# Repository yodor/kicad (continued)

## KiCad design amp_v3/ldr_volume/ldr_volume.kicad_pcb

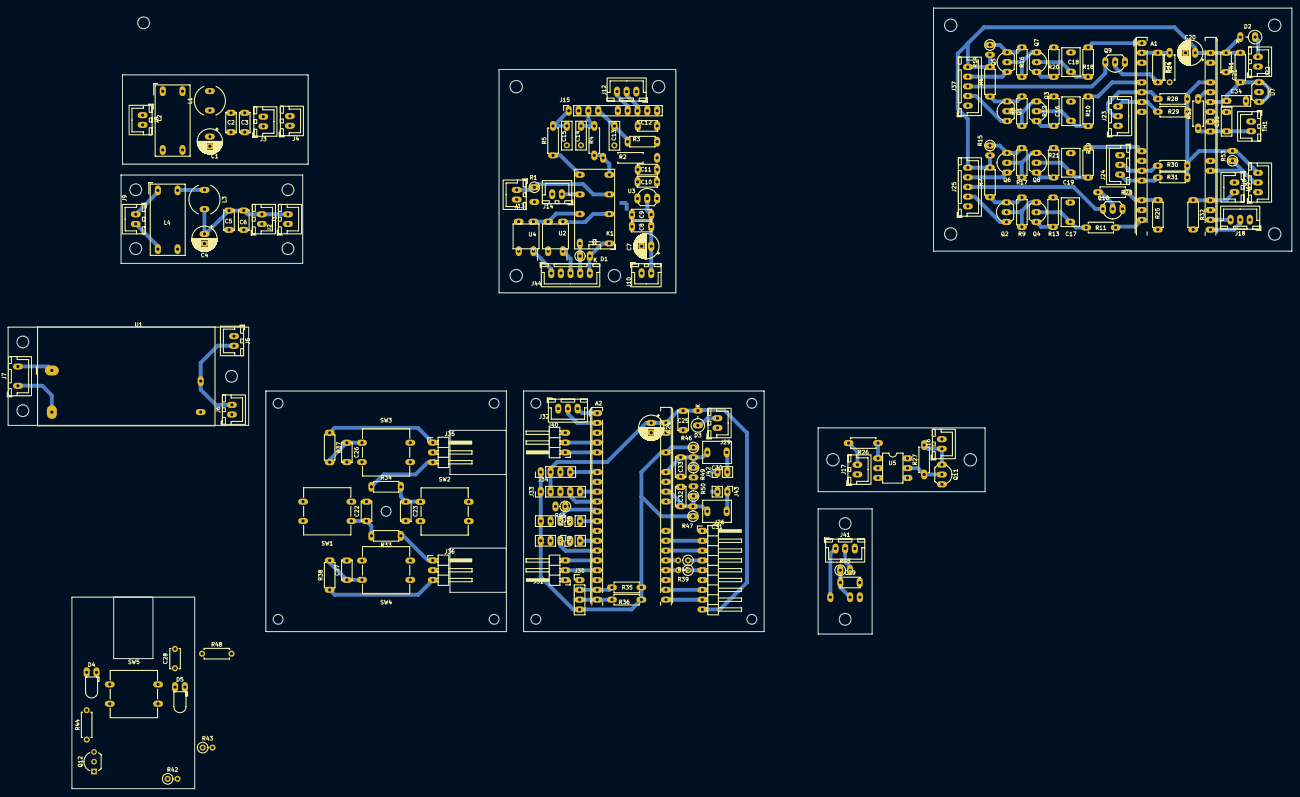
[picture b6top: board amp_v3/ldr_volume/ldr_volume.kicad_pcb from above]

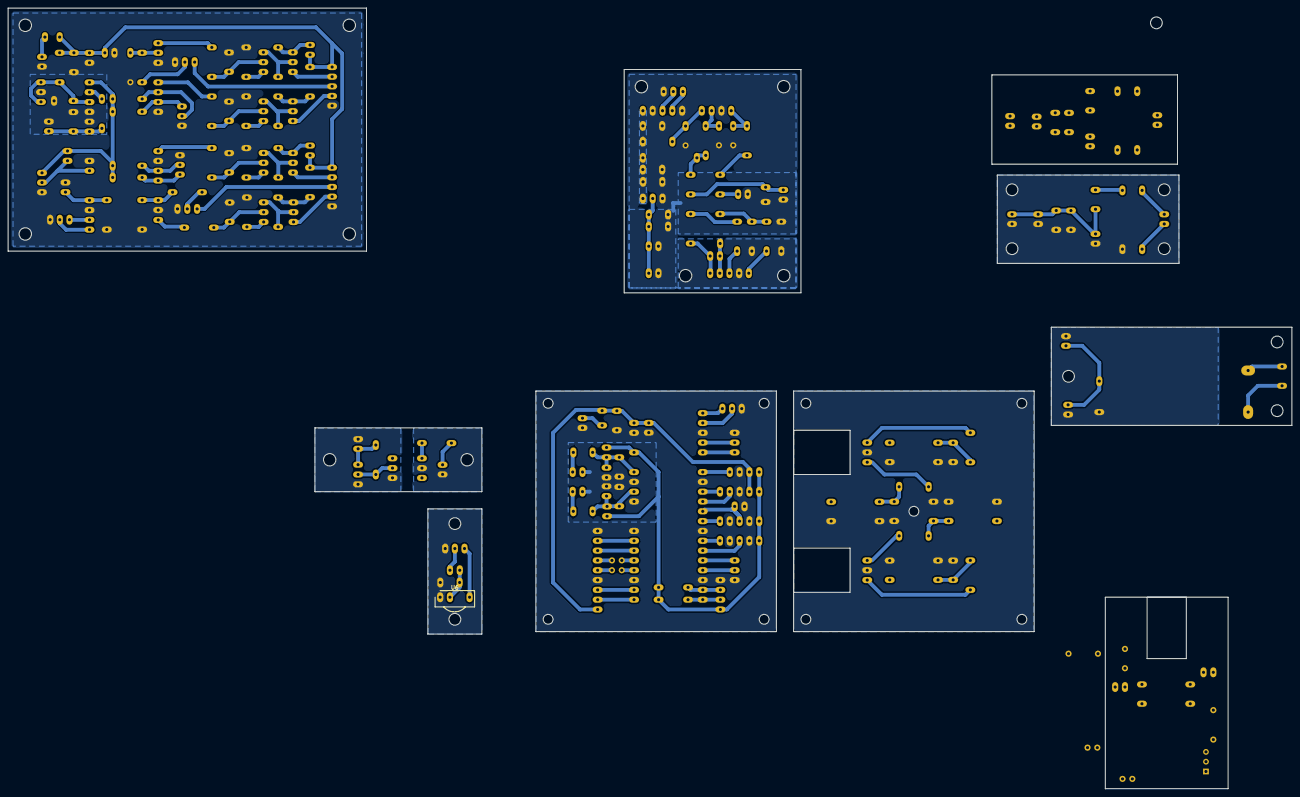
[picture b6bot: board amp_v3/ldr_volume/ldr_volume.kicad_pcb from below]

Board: 2 copper layers, 332.1 x 201.9 mm, 171 parts (5 on the bottom side), 122 nets.

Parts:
A1, A2: RaspberryPi_Pico_W; RaspberryPi_Pico_Common_THT
C1, C4: 100uF (low esr); CP_Radial_D6.3mm_P2.50mm
C2, C5: 10uF; C_Disc_D5.0mm_W2.5mm_P5.00mm
C3, C6: 100nF (X7R); C_Disc_D5.0mm_W2.5mm_P5.00mm
C7: 100uF; CP_Radial_D6.3mm_P2.50mm
C8, C11: 1uF; C_Disc_D5.0mm_W2.5mm_P5.00mm
C9, C10, C12, C21, C22, C23, C25, C26, C27, C28, C29: 100nF; C_Disc_D5.0mm_W2.5mm_P5.00mm
C13, C14, C15, C34, C35: 100nF; C_Rect_L7.2mm_W2.5mm_P5.00mm_FKS2_FKP2_MKS2_MKP2
C16, C17, C18, C19: 1uF; C_Rect_L7.2mm_W4.5mm_P5.00mm_FKS2_FKP2_MKS2_MKP2
C20, C24: 100uF low; CP_Radial_D6.3mm_P2.50mm
C30, C31: 1uF; C_Rect_L7.2mm_W5.5mm_P5.00mm_FKS2_FKP2_MKS2_MKP2
C32, C33: 10nF; C_Disc_D5.0mm_W2.5mm_P5.00mm
D1: 1n4007; D_DO-35_SOD27_P2.54mm_Vertical_CathodeUp
D2, D3: 1n5819; D_DO-41_SOD81_P3.81mm_Vertical_CathodeUp
D4: LED; LED_D3.0mm_Horizontal_O1.27mm_Z2.0mm
D5: WHITE LED; LED_D3.0mm_Horizontal_O1.27mm_Z2.0mm
J1: PWR1; JST_XH_B2B-XH-A_1x02_P2.50mm_Vertical
J2: PWR2; JST_XH_B2B-XH-A_1x02_P2.50mm_Vertical
J3, J5: PWR3; JST_XH_B2B-XH-A_1x02_P2.50mm_Vertical
J4, J6: PWR4; JST_XH_B2B-XH-A_1x02_P2.50mm_Vertical
J7: Conn_01x03_Pin; JST_XH_B3B-XH-A_1x03_P2.50mm_Vertical
J8, J9: 5V_IN; JST_XH_B2B-XH-A_1x02_P2.50mm_Vertical
J10: 5v_in; JST_XH_B2B-XH-A_1x02_P2.50mm_Vertical
J12, J24: I2C_R; JST_XH_B3B-XH-A_1x03_P2.50mm_Vertical
J13: A_IN; JST_XH_B2B-XH-A_1x02_P2.50mm_Vertical
J14: A_OUT; JST_XH_B2B-XH-A_1x02_P2.50mm_Vertical
J15: ADS1115; PinSocket_1x10_P2.54mm_Vertical
J16: MUTE_OUT; JST_XH_B2B-XH-A_1x02_P2.50mm_Vertical
J17, J19: MUTE; JST_XH_B2B-XH-A_1x02_P2.50mm_Vertical
J18, J40: UART; JST_XH_B3B-XH-A_1x03_P2.50mm_Vertical
J22, J29: PWR_IN; JST_XH_B2B-XH-A_1x02_P2.50mm_Vertical
J23: I2C_L; JST_XH_B3B-XH-A_1x03_P2.50mm_Vertical
J25: LDR_R; JST_XH_B5B-XH-A_1x05_P2.50mm_Vertical
J26: TFT; PinHeader_1x09_P2.54mm_Horizontal
J27: PWR_BTN; PinHeader_1x02_P2.54mm_Vertical
J28: PWR_BTN_LED; PinHeader_1x02_P2.54mm_Vertical
J30: I2C; PinHeader_1x04_P2.54mm_Vertical
J31: BTN_VOL; PinHeader_1x03_P2.54mm_Horizontal
J32: BTN_MENU; PinHeader_1x03_P2.54mm_Horizontal
J33: ALPS; PinHeader_1x05_P2.54mm_Vertical
J34: PWR_RLY; PinHeader_1x04_P2.54mm_Vertical
J35: BTN_EXT1; PinHeader_1x03_P2.54mm_Horizontal
J36: BTN_EXT2; PinHeader_1x03_P2.54mm_Horizontal
J37, J44: LDR_L; JST_XH_B5B-XH-A_1x05_P2.50mm_Vertical
J38: IR; PinHeader_1x03_P2.54mm_Vertical
J39: MUTE; PinHeader_1x03_P2.54mm_Vertical
J41: IR_SENSOR; JST_XH_B3B-XH-A_1x03_P2.50mm_Vertical
J42: S_AIN_L; PinHeader_1x02_P2.54mm_Vertical
J43: S_AIN_R; PinHeader_1x02_P2.54mm_Vertical
K1: G5V-2; Relay_DPDT_Omron_G5V-2
L1, L3: 10uH; L_Radial_D7.8mm_P5.00mm_Fastron_07HCP
L2: RN202-0.3-02-12M; Choke_Schaffner_RN202-04-8.8x18.2mm
L4: RN-202-1/02; Choke_Schaffner_RN202-04-8.8x18.2mm
NT1: ATOGNDA; NetTie-2_SMD_Pad1.0o
NT2: AUDIOGND_TO_GNDA; NetTie-2_SMD_Pad1.0o
NT3, NT4: NetTie_2; NetTie-2_SMD_Pad1.0o
Q1, Q2, Q5, Q6: BC557; TO-92_Inline_Wide
Q3, Q4, Q7, Q8, Q11, Q12: BC547; TO-92_Inline_Wide
Q9, Q10: 2N7000; TO-92_Inline_Wide
R1: 1M; R_Axial_DIN0207_L6.3mm_D2.5mm_P2.54mm_Vertical
R2, R10, R11, R18, R19, R24, R25, R32: 10K; R_Axial_DIN0207_L6.3mm_D2.5mm_P7.62mm_Horizontal
R3, R4, R5, R27: 1K; R_Axial_DIN0207_L6.3mm_D2.5mm_P7.62mm_Horizontal
R6, R7: 120; R_Axial_DIN0207_L6.3mm_D2.5mm_P7.62mm_Horizontal
R8, R9, R16, R17, R52: 100K; R_Axial_DIN0207_L6.3mm_D2.5mm_P7.62mm_Horizontal
R12, R13, R20, R21: 68K; R_Axial_DIN0207_L6.3mm_D2.5mm_P7.62mm_Horizontal
R14, R15: 120; R_Axial_DIN0207_L6.3mm_D2.5mm_P2.54mm_Vertical
R22, R23: 100R; R_Axial_DIN0207_L6.3mm_D2.5mm_P7.62mm_Horizontal
R26: 100; R_Axial_DIN0207_L6.3mm_D2.5mm_P7.62mm_Horizontal
R28, R29, R30, R31, R35, R36: 4.7K; R_Axial_DIN0207_L6.3mm_D2.5mm_P7.62mm_Horizontal
R33, R34, R37, R38, R44, R48: 1k; R_Axial_DIN0207_L6.3mm_D2.5mm_P7.62mm_Horizontal
R39, R40: 22; R_Axial_DIN0207_L6.3mm_D2.5mm_P2.54mm_Vertical
R41, R46, R47, R49, R50: 10K; R_Axial_DIN0207_L6.3mm_D2.5mm_P2.54mm_Vertical
R42, R43, R45: 100; R_Axial_DIN0207_L6.3mm_D2.5mm_P2.54mm_Vertical
R51: 2.2K; R_Axial_DIN0207_L6.3mm_D2.5mm_P7.62mm_Horizontal
R53: 4.7K; R_Axial_DIN0207_L6.3mm_D2.5mm_P2.54mm_Vertical
SW1: SW_LT; SW_SPST_Omron_B3F-50xx
SW2: SW_RT; SW_SPST_Omron_B3F-50xx
SW3: SW_UP; SW_SPST_Omron_B3F-50xx
SW4: SW_DN; SW_SPST_Omron_B3F-50xx
SW5: SW_PWR; SW_SPST_Omron_B3F-50xx
TH1: B3950; JST_XH_B2B-XH-A_1x02_P2.50mm_Vertical
U1: IRM-10-5; Converter_ACDC_MeanWell_IRM-10-xx_THT
U2: NSL-32-SR3-Rseries; Luna_NSL-32
U3: MCP1700x-330xxTO; TO-92_Inline_Wide
U4: NSL-32-SR3-Rshunt; Luna_NSL-32
U5: 4N25; DIP-6_W7.62mm
U6: TSOP312xx; Vishay_CAST-3Pin
U7: TL431LP; TO-92_Inline_Wide
U8: DS18B20; JST_XH_B3B-XH-A_1x03_P2.50mm_Vertical

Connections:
/5V power/5V_IRM: J5.2, J6.2, J8.1, J9.1, L2.1, L4.1, U1.4 (+Vo)
/5V power/5V_analog: C1.1, C2.1, C3.1, J3.2, J4.2, L1.2
/5V power/5V_board1: C4.1, C5.1, C6.1, J1.2, J2.2, L3.2
/5V power/GND_IRM: J5.1, J6.1, J8.2, J9.2, L2.3, L4.3, U1.3 (-Vo)
/5V power/gnd_analog: C1.2, C2.2, C3.2, J3.1, J4.1, L2.4
/LDR Board/5v_ads: C7.1, C8.1, C9.1, J10.2, U3.2 (VI)
/LDR Board/5v_local: D1.1 (K), J44.5, K1.1
/LDR Board/A0: C13.1, J15.4, R3.1
/LDR Board/A1: C14.1, J15.3, R4.1
/LDR Board/A3: C15.1, J15.1, R5.1
/LDR Board/ADS_VDD: C10.1, C11.1, C12.1, J15.10, R2.2, R3.2, U3.3 (VO)
/LDR Board/AUDIO_IN: J13.1, K1.6, R1.1
/LDR Board/AUDIO_OUT: J14.1, K1.11
/LDR Board/COIL_NEG: D1.2 (A), J44.4, K1.16
/LDR Board/MIDDLE_JUNCTION: K1.9, R5.2
/LDR Board/SCL: J12.2, J15.8
/LDR Board/SDA: J12.3, J15.7
/LDR Board/SERIAL_POS: J44.3, U2.1 (A)
/LDR Board/SHUNT_POS: J44.1, U4.1 (A)
/LDR Board/TOP_JUNCTION: K1.8, R2.1, R4.2
/LDR Board/gnd_analog: C7.2, C8.2, C9.2, J10.1, NT1.1
/LDR Driver/3.3V_PICO: A1.36 (3V3), R28.1, R29.1, R30.1, R31.1, R53.2, U8.3 (V_{DD})
/LDR Driver/5V_board1: D2.2 (A), J22.2
/LDR Driver/5v_local: A1.39 (VSYS), C20.1, C21.1, D2.1 (K), J25.5, J37.5, R6.2, R7.2, R14.2, R15.2, R51.2
/LDR Driver/ADC_NTC: A1.31 (GPIO26_ADC0), C35.1, R52.1, TH1.2
/LDR Driver/ADC_TL431REF: A1.34 (GPIO28_ADC2), C34.1, R51.1, U7.1 (REF), U7.3 (K)
/LDR Driver/ADC_VREF: A1.35 (ADC_VREF), R52.2
/LDR Driver/AGND_PICO: A1.32 (GPIO27_ADC1), A1.33 (AGND), C34.2, C35.2, TH1.1, U7.2 (A)
/LDR Driver/AMP_GND_PIN: J16.2, Q11.3 (E), U5.4
/LDR Driver/AMP_MUTE_PIN: J16.1, Q11.1 (C), R27.2
/LDR Driver/COIL_CTRL_L: A1.2 (GPIO1), R22.1, R24.1
/LDR Driver/COIL_CTRL_R: A1.17 (GPIO13), R23.1, R25.1
/LDR Driver/COIL_L: J37.3, Q9.3 (D)
/LDR Driver/COIL_R: J25.3, Q10.3 (D)
/LDR Driver/DQ_IN: A1.27 (GPIO21), R53.1, U8.2 (DQ)
/LDR Driver/MUTE_CTRL: A1.24 (GPIO18), J17.2, J19.2, R26.2, R32.1
/LDR Driver/PWM_SER_L: A1.1 (GPIO0), R18.2
/LDR Driver/PWM_SER_R: A1.12 (GPIO9), R19.2
/LDR Driver/PWM_SHUNT_L: A1.5 (GPIO3), R10.2
/LDR Driver/PWM_SHUNT_R: A1.19 (GPIO14), R11.2
/LDR Driver/SCL_L: A1.7 (GPIO5), J23.3, R29.2
/LDR Driver/SCL_R: A1.15 (GPIO11), J24.3, R31.2
/LDR Driver/SDA_L: A1.6 (GPIO4), J23.2, R28.2
/LDR Driver/SDA_R: A1.14 (GPIO10), J24.2, R30.2
/LDR Driver/SERIAL_L: J37.4, Q5.1 (C)
/LDR Driver/SERIAL_R: J25.4, Q6.1 (C)
/LDR Driver/SHUNT_L: J37.2, Q1.1 (C)
/LDR Driver/SHUNT_R: J25.2, Q2.1 (C)
/LDR Driver/UART_RX: A1.22 (GPIO17), J18.3
/LDR Driver/UART_TX: A1.21 (GPIO16), J18.2
/Main Board/3.3V_PICO: A2.36 (3V3), J30.4, J33.1, J34.1, J38.3, J39.3, J41.2, R35.1, R36.1, R45.2, R46.1, R47.1
/Main Board/5V_board1: D3.2 (A), J29.2
/Main Board/5v_local: A2.39 (VSYS), C24.1, C25.1, D3.1 (K), J26.9, J33.2, J34.2, R42.2, R43.2
/Main Board/ADC_L: A2.34 (GPIO28_ADC2), C30.2, C33.1, R46.2, R49.1
/Main Board/ADC_R: A2.32 (GPIO27_ADC1), C31.2, C32.2, R47.2, R50.1
/Main Board/AGND_L: J42.1, NT4.1
/Main Board/AGND_PICO: A2.31 (GPIO26_ADC0), A2.33 (AGND), C32.1, C33.2, NT3.2, NT4.2, R49.2, R50.2
/Main Board/AGND_R: J43.2, NT3.1
/Main Board/ALPS_L: A2.10 (GPIO7), J33.4
/Main Board/ALPS_R: A2.9 (GPIO6), J33.5
/Main Board/AUDIO_L: C30.1, J42.2
/Main Board/AUDIO_R: C31.1, J43.1
/Main Board/BTN_DN: A2.17 (GPIO13), J31.2, J36.3, R38.1
/Main Board/BTN_LT: A2.16 (GPIO12), J31.3, J36.1, R33.1
/Main Board/BTN_RT: A2.5 (GPIO3), J32.1, J35.3, R34.1
/Main Board/BTN_UP: A2.4 (GPIO2), J32.2, J35.1, R37.1
/Main Board/IR: A2.15 (GPIO11), J39.1, J41.1, U6.3 (OUT)
/Main Board/MUTE_CTRL: A2.11 (GPIO8), J38.1, R41.1
/Main Board/PWR_BTN: A2.14 (GPIO10), J27.2, R44.1
/Main Board/PWR_BTN_LED: A2.12 (GPIO9), J28.2
/Main Board/RLCTRL: A2.7 (GPIO5), J34.4
/Main Board/SCL: A2.20 (GPIO15), J30.3, R36.2
/Main Board/SDA: A2.19 (GPIO14), J30.2, R35.2
/Main Board/TFT_BLK: A2.27 (GPIO21), J26.2
/Main Board/TFT_CS: A2.22 (GPIO17), J26.7
/Main Board/TFT_DC: A2.21 (GPIO16), J26.8
/Main Board/TFT_RST: A2.26 (GPIO20), J26.3
/Main Board/TFT_SCL: J26.5, R39.1
/Main Board/TFT_SDA: J26.4, R40.1
/Main Board/UART_RX: A2.2 (GPIO1), J40.2
/Main Board/UART_TX: A2.1 (GPIO0), J40.3
AUDIO_GND: J13.2, J14.2, NT2.1, R1.2, U4.3 (R)
GNDA: C10.2, C11.2, C12.2, C13.2, C14.2, C15.2, J12.1, J15.2, J15.6, J15.9, NT1.2, NT2.2, U3.1 (GND)
GNDD: A1.3 (GND), A1.8 (GND), A1.13 (GND), A1.18 (GND), A1.23 (GND), A1.28 (GND), A1.38 (GND), A2.3 (GND), A2.8 (GND), A2.13 (GND), A2.18 (GND), A2.23 (GND), A2.28 (GND), A2.38 (GND), C4.2, C5.2, C6.2, C16.2, C17.2, C18.2, C19.2, C20.2, C21.2, C22.2, C23.2, C24.2, C25.2, C26.2, C27.2, C28.2, C29.2, J1.1, J2.1, J17.1, J18.1, J19.1, J22.1, J23.1, J24.1, J25.1, J26.1, J26.6, J27.1, J28.1, J29.1, J30.1, J31.1, J32.3, J33.3, J34.3, J35.2, J36.2, J37.1, J38.2, J39.2, J40.1, J41.3, J44.2, L4.4, Q9.1 (S), Q10.1 (S), Q12.3 (E), R12.2, R13.2, R20.1, R21.1, R24.2, R25.2, R32.2, R41.2, SW1.2, SW2.2, SW3.2, SW4.2, SW5.2, U2.2 (K), U4.2 (K), U5.2, U6.1 (GND), U8.1 (GND)
unnamed: A2.24 (GPIO18), R39.2
unnamed: A2.25 (GPIO19), R40.2
unnamed: C22.1, R33.2, SW1.1
unnamed: C23.1, R34.2, SW2.1
unnamed: C26.1, R37.2, SW3.1
unnamed: C27.1, R38.2, SW4.1
unnamed: C28.1, R44.2, SW5.1
unnamed: D4.2 (A), R42.1
unnamed: D4.1 (K), D5.1 (K), Q12.1 (C)
unnamed: D5.2 (A), R43.1
unnamed: J7.1, U1.2 (AC/L)
unnamed: J7.3, U1.1 (AC/N)
unnamed: K1.4, U2.4 (R)
unnamed: K1.13, U2.3 (R), U4.4 (R)
unnamed: L1.1, L2.2
unnamed: L3.1, L4.2
unnamed: Q1.2 (B), Q3.1 (C), R8.1
unnamed: Q1.3 (E), R6.1, R8.2
unnamed: Q2.2 (B), Q4.1 (C), R9.1
unnamed: Q2.3 (E), R7.1, R9.2
unnamed: C16.1, Q3.2 (B), R10.1
unnamed: Q3.3 (E), R12.1
unnamed: C17.1, Q4.2 (B), R11.1
unnamed: Q4.3 (E), R13.1
unnamed: Q5.2 (B), Q7.1 (C), R16.1
unnamed: Q5.3 (E), R14.1, R16.2
unnamed: Q6.2 (B), Q8.1 (C), R17.1
unnamed: Q6.3 (E), R15.1, R17.2
unnamed: C18.1, Q7.2 (B), R18.1
unnamed: Q7.3 (E), R20.2
unnamed: C19.1, Q8.2 (B), R19.1
unnamed: Q8.3 (E), R21.2
unnamed: Q9.2 (G), R22.2
unnamed: Q10.2 (G), R23.2
unnamed: Q11.2 (B), R27.1, U5.5
unnamed: Q12.2 (B), R48.2
unnamed: R26.1, U5.1
unnamed: C29.1, R45.1, U6.2 (Vs)
